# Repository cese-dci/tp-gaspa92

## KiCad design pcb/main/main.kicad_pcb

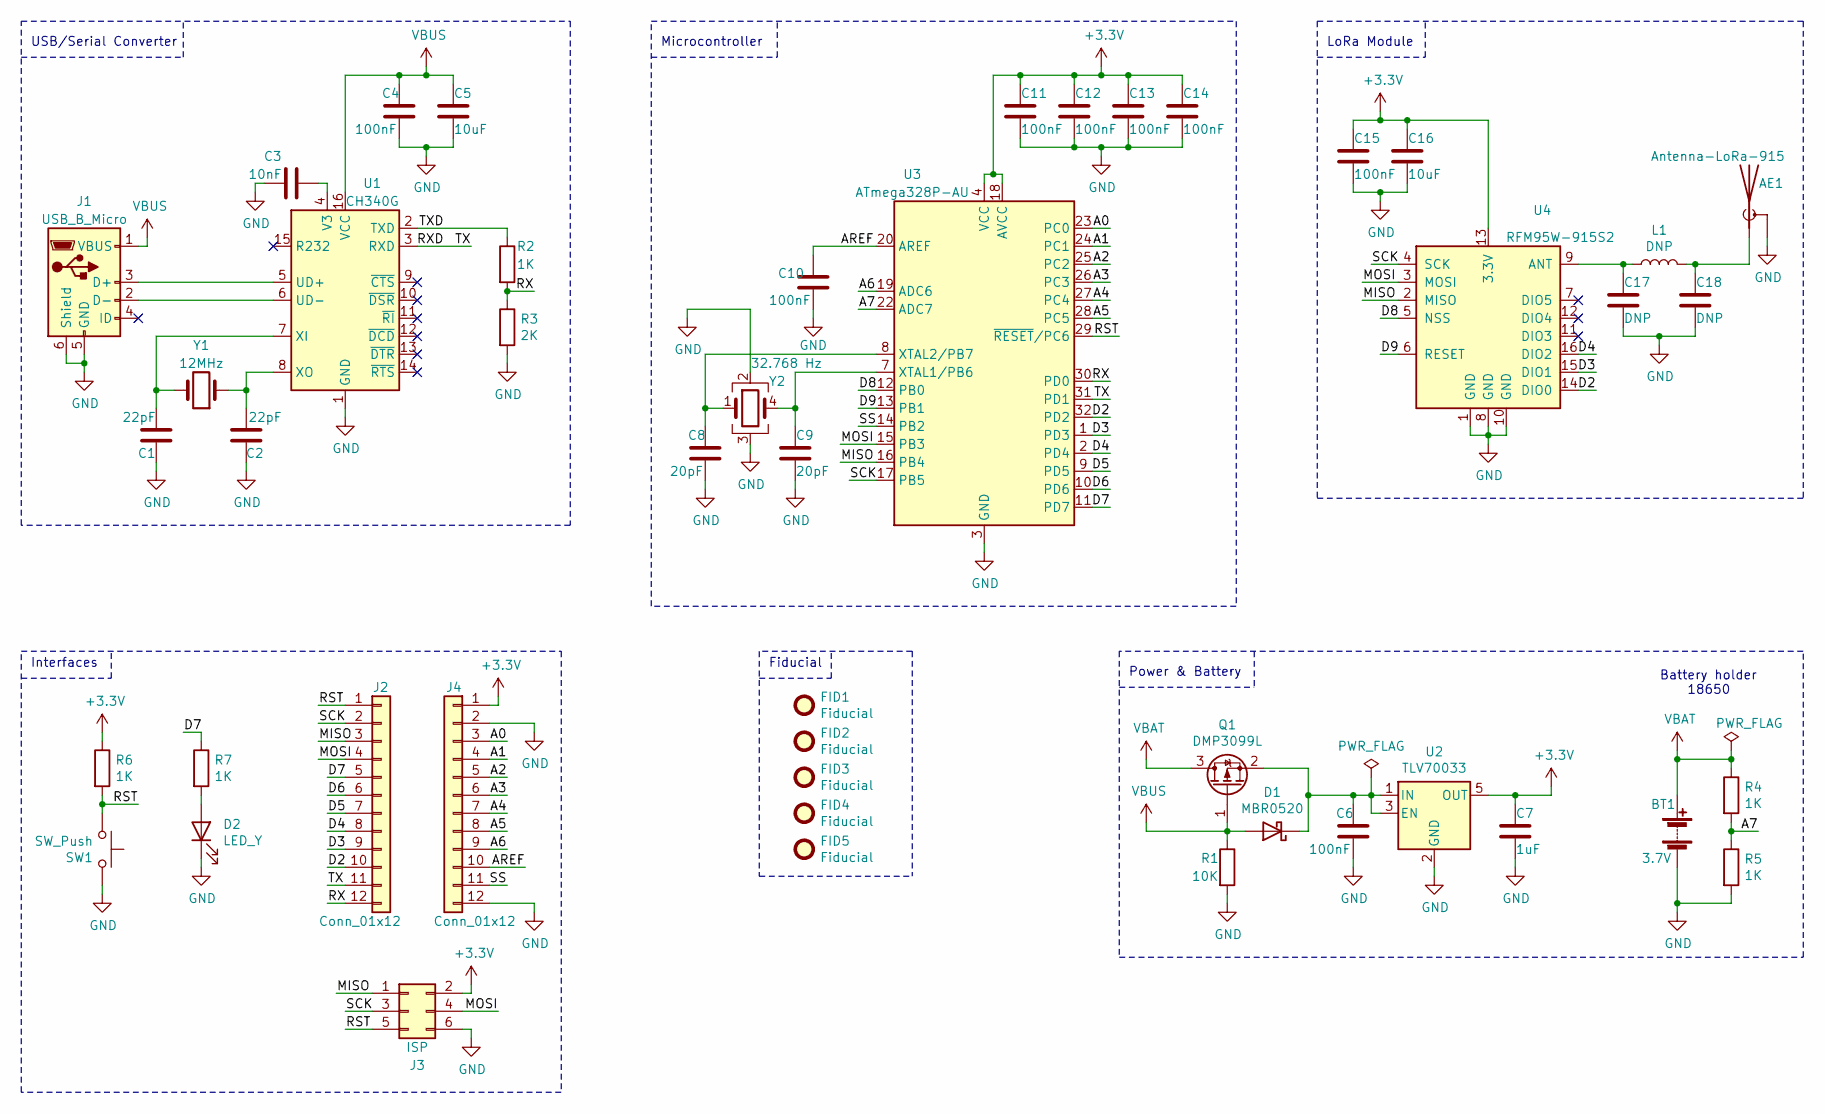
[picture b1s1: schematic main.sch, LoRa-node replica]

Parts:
AE1: Antenna-LoRa-915; antenna-lora-915
BT1: 3.7V; BatteryHolder_MPD_BH-18650-PC2; Digikey PN BH-18650-PC-ND
C1, C2: 22pF; C_0805_2012Metric_Pad1.18x1.45mm_HandSolder
C3: 10nF; C_0805_2012Metric_Pad1.18x1.45mm_HandSolder
C4, C6, C10, C11, C12, C13, C14, C15: 100nF; C_0805_2012Metric_Pad1.18x1.45mm_HandSolder
C5, C16: 10uF; C_0805_2012Metric_Pad1.18x1.45mm_HandSolder
C7: 1uF; C_0805_2012Metric_Pad1.18x1.45mm_HandSolder
C8, C9: 20pF; C_0805_2012Metric_Pad1.18x1.45mm_HandSolder
C17, C18: DNP; C_0805_2012Metric_Pad1.18x1.45mm_HandSolder
D1: MBR0520; D_SOD-123; Digikey PN MBR0520LT1GOSCT-ND
D2: LED_Y; LED_0805_2012Metric_Pad1.15x1.40mm_HandSolder
FID1, FID2, FID3, FID4, FID5: Fiducial; Fiducial_0.5mm_Mask1.5mm
J1: USB_B_Micro; USB_Micro-B_Molex_47346-0001; Digikey PN WM17141CT-ND
J2, J4: Conn_01x12; PinHeader_1x12_P2.54mm_Vertical
J3: ISP; PinHeader_2x03_P2.54mm_Vertical
L1: DNP; L_0805_2012Metric_Pad1.15x1.40mm_HandSolder
Q1: DMP3099L; SOT-23; Digikey PN DMP3099L-7DICT-ND
R1: 10K; R_0805_2012Metric_Pad1.20x1.40mm_HandSolder
R2, R4, R5, R6, R7: 1K; R_0805_2012Metric_Pad1.20x1.40mm_HandSolder
R3: 2K; R_0805_2012Metric_Pad1.20x1.40mm_HandSolder
SW1: SW_Push; SW_PUSH_6mm_H4.3mm
U1: CH340G; SOIC-16_3.9x9.9mm_P1.27mm
U2: TLV70033; SOT-23-5; Digikey PN 296-25276-1-ND
U3: ATmega328P-AU; TQFP-32_7x7mm_P0.8mm; Digikey PN ATMEGA328P-AU-ND
U4: RFM95W-915S2; HOPERF_RFM9XW_SMD
Y1: 12MHz; Crystal_SMD_HC49-SD; Digikey PN 1923-1541-1-ND
Y2: 32.768 Hz; Crystal_SMD_Abracon_ABS25-4Pin_8.0x3.8mm; Digikey PN 535-9166-1-ND

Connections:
+3V3: C7.1, C11.1, C12.1, C13.1, C14.1, C15.1, C16.1, J3.2, J4.1, R6.1, U2.5 (OUT), U3.4 (VCC), U3.6 (VCC), U3.18 (AVCC), U4.13 (3.3V)
/A0: J4.3, U3.23 (PC0)
/A1: J4.4, U3.24 (PC1)
/A2: J4.5, U3.25 (PC2)
/A3: J4.6, U3.26 (PC3)
/A4: J4.7, U3.27 (PC4)
/A5: J4.8, U3.28 (PC5)
/A6: J4.9, U3.19 (ADC6)
/A7: R4.2, R5.1, U3.22 (ADC7)
/AREF: C10.1, J4.10, U3.20 (AREF)
/D2: J2.10, U3.32 (PD2), U4.14 (DIO0)
/D3: J2.9, U3.1 (PD3), U4.15 (DIO1)
/D4: J2.8, U3.2 (PD4), U4.16 (DIO2)
/D5: J2.7, U3.9 (PD5)
/D6: J2.6, U3.10 (PD6)
/D7: J2.5, R7.1, U3.11 (PD7)
/D8: U3.12 (PB0), U4.5 (NSS)
/D9: U3.13 (PB1), U4.6 (RESET)
/MISO: J2.3, J3.1, U3.16 (PB4), U4.2 (MISO)
/MOSI: J2.4, J3.4, U3.15 (PB3), U4.3 (MOSI)
/RST: J2.1, J3.5, R6.2, SW1.1, U3.29 (~RESET~/PC6)
/RX: J2.12, R2.2, R3.1, U3.30 (PD0)
/RXD: J2.11, U1.3 (RXD), U3.31 (PD1)
/SCK: J2.2, J3.3, U3.17 (PB5), U4.4 (SCK)
/SS: J4.11, U3.14 (PB2)
/TXD: R2.1, U1.2 (TXD)
GND: AE1.2 (Shield), BT1.2 (-), C1.1, C2.1, C3.1, C4.2, C5.2, C6.2, C7.2, C8.2, C9.2, C10.2, C11.2, C12.2, C13.2, C14.2, C15.2, C16.2, C17.2, C18.2, D2.1 (K), J1.5 (GND), J1.6 (Shield), J3.6, J4.2, J4.12, R1.2, R3.2, R5.2, SW1.2, U1.1 (GND), U2.2 (GND), U3.3 (GND), U3.5 (GND), U3.21 (GND), U4.1 (GND), U4.8 (GND), U4.10 (GND), Y2.2, Y2.3
unnamed: AE1.1 (A), C18.1, L1.2
unnamed: C1.2, U1.7 (XI), Y1.2
unnamed: C2.2, U1.8 (XO), Y1.1
unnamed: C3.2, U1.4 (V3)
unnamed: C6.1, D1.1 (K), Q1.2 (S), U2.1 (IN), U2.3 (EN)
unnamed: C8.1, U3.8 (XTAL2/PB7), Y2.1
unnamed: C9.1, U3.7 (XTAL1/PB6), Y2.4
unnamed: C17.1, L1.1, U4.9 (ANT)
unnamed: D2.2 (A), R7.2
unnamed: J1.2 (D-), U1.6 (UD-)
unnamed: J1.3 (D+), U1.5 (UD+)
VBAT: BT1.1 (+), Q1.3 (D), R4.1
VBUS: C4.1, C5.1, D1.2 (A), J1.1 (VBUS), Q1.1 (G), R1.1, U1.16 (VCC)

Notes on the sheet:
Microcontroller
USB/Serial Converter
LoRa Module
Power & Battery
Interfaces
Battery holder 18650
Fiducial

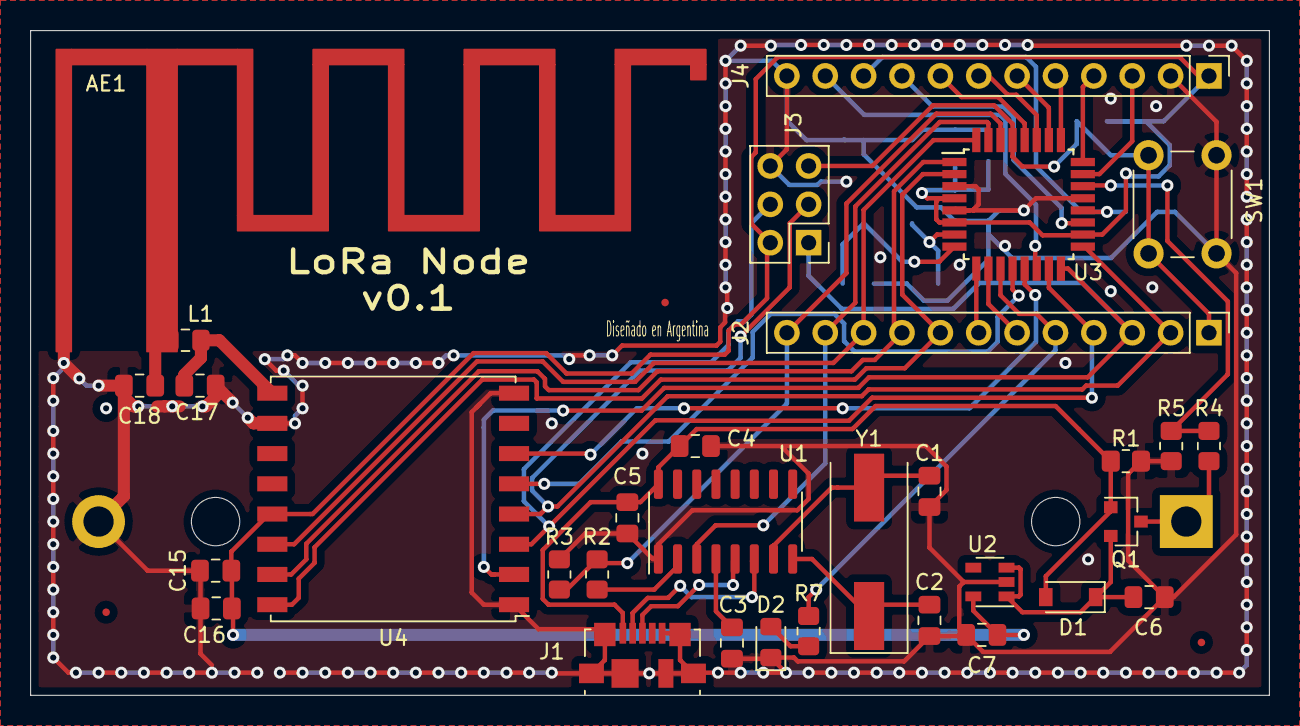
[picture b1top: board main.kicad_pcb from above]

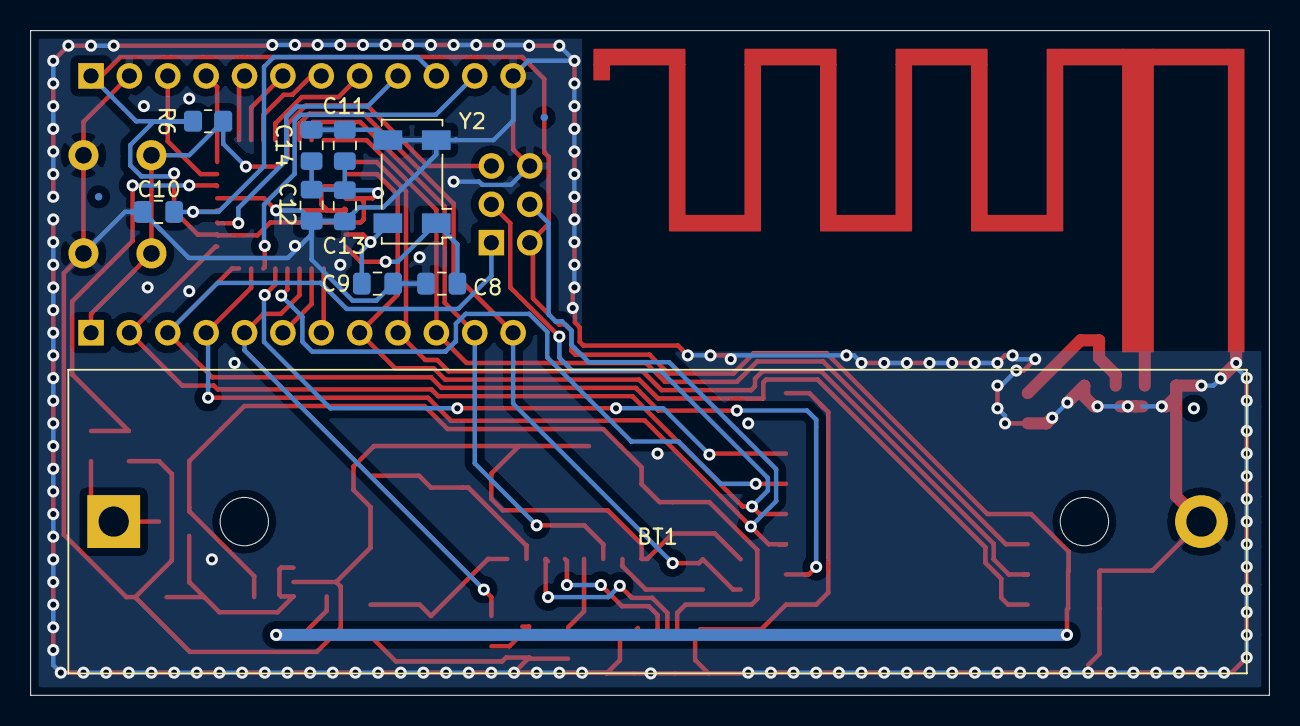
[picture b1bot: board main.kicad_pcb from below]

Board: 2 copper layers, 82.0 x 44.0 mm, 47 parts (12 on the bottom side), 40 nets.

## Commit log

2021-03-18 Primer commit
2021-03-20 Added complete schematic
2021-03-20 Added schematic plot in PDF
2021-03-20 Fix README.md
2021-03-20 Minor fixes in schematic
2021-03-20 Update schematic plot
2021-03-20 Added DNP for antenna matching components values
2021-03-20 Schematic plot updated
2021-04-14 Footprints assigned
2021-04-14 Reference designs documentation added
2021-04-15 Fix Rev field
2021-04-16 Added custom symbols lib
2021-04-17 Added antenna footprint
2021-04-17 Fix previous commit
2021-04-23 Fix - Correcciones solicitadas
2021-04-23 PCB added
2021-04-24 Fix fiducials and annotations
2021-04-27 Correcciones

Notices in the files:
pcb/main/main.kicad_pcb:
Creative Commons Attribution-ShareAlike 4.0 International License
